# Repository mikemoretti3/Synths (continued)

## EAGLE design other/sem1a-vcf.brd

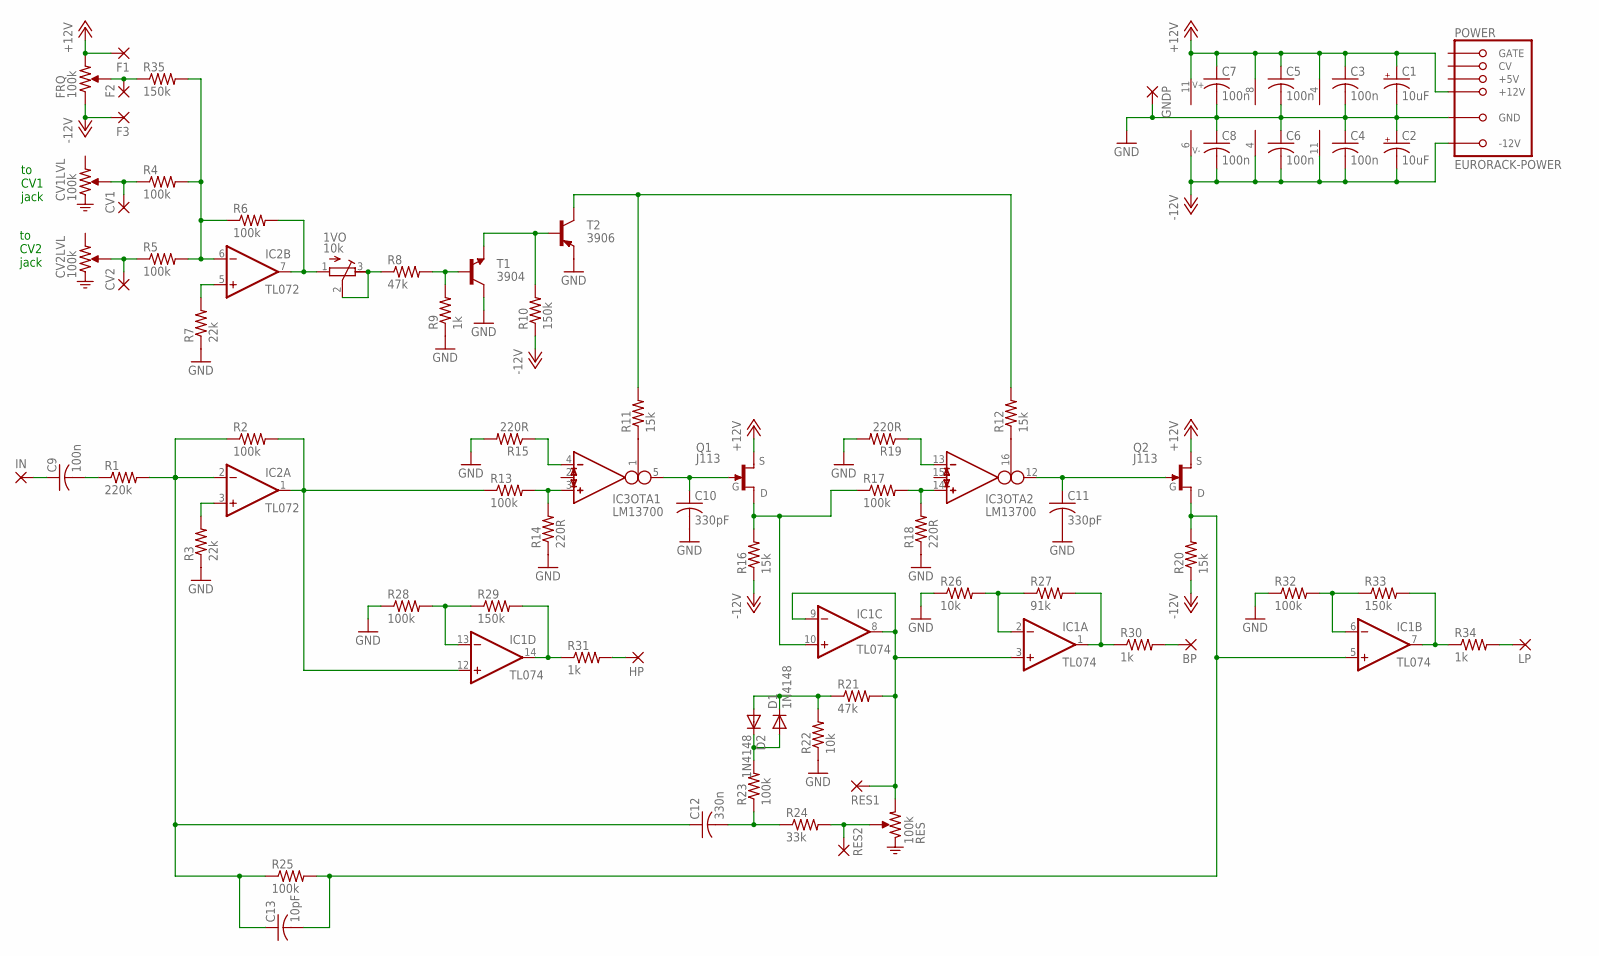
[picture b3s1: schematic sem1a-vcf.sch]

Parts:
1VO: 10k; RTRIM64W
BP: 2,54/1,0
C1, C2: 10uF; E2,5-5
C3, C4, C5, C6, C7, C8: 100n; C025-025X050
C9: 100n; C050-025X075
C10, C11: 330pF; C050-025X075
C12: 330n; C050-025X075
C13: 10pF; C050-025X075
CV1, CV2: 2,54/1,0
D1, D2: 1N4148; DO35-7
F1, F2, F3: 2,54/1,0
GNDP: 2,54/1,0
HP: 2,54/1,0
IC1: TL074; DIL14
IC2: TL072; DIL08
IC3: LM13700; DIL16
IN: 2,54/1,0
LP: 2,54/1,0
POWER: EURORACK-POWER; PINSHRD_PTH_2X8
Q1, Q2: J113; TO92-EBC
R1: 220k; 0207/10
R2, R6: 100k; 0207/2V
R3, R7: 22k; 0207/10
R4, R5, R13, R17, R23, R25, R28, R32: 100k; 0207/10
R8, R21: 47k; 0207/10
R9, R30, R31, R34: 1k; 0207/10
R10, R35: 150k; 0207/10
R11, R12, R16, R20: 15k; 0207/10
R14, R15, R18, R19: 220R; 0207/10
R22, R26: 10k; 0207/10
R24: 33k; 0207/10
R27: 91k; 0207/2V
R29, R33: 150k; 0207/2V
RES1, RES2: 2,54/1,0
T1: 3904; TO92-EBC
T2: 3906; TO92-EBC

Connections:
+12V: C1.+, C3.1, C5.1, C7.1, F1.1, IC1.4 (V+), IC2.8 (V+), IC3.11 (7), POWER.+12V@1 (+12V), POWER.+12V@2 (+12V), Q1.E (S), Q2.E (S)
-12V: C2.-, C4.2, C6.2, C8.2, F3.1, IC1.11 (V-), IC2.4 (V-), IC3.6 (4), POWER.-12V@1 (-12V), POWER.-12V@2 (-12V), R10.1, R16.1, R20.1
GND: C1.-, C2.+, C3.2, C4.1, C5.2, C6.1, C7.2, C8.1, C10.2, C11.2, GNDP.1, POWER.GND@1 (GND), POWER.GND@2 (GND), POWER.GND@3 (GND), POWER.GND@4 (GND), POWER.GND@5 (GND), POWER.GND@6 (GND), R3.1, R7.1, R9.1, R14.1, R15.2, R18.1, R19.2, R22.1, R26.1, R28.1, R32.1, T1.C, T2.E
unnamed: CV1.1, R4.1
unnamed: CV2.1, R5.1
unnamed: IC2.6 (-IN), R4.2, R5.2, R6.1, R35.2
unnamed: 1VO.2 (S), 1VO.3 (E), R8.1
unnamed: R10.2, T1.E, T2.B
unnamed: IC1.3 (+IN), IC1.8 (OUT), IC1.9 (-IN), R21.2, RES1.1
unnamed: R24.2, RES2.1
unnamed: R8.2, R9.2, T1.B
unnamed: IC3.1 (I_BIAS), R11.1
unnamed: C9.1, IN.1
unnamed: C9.2, R1.1
unnamed: C12.1, C13.1, IC2.2 (-IN), R1.2, R2.1, R25.1
unnamed: IC1.12 (+IN), IC2.1 (OUT), R2.2, R13.1
unnamed: IC2.3 (+IN), R3.2
unnamed: IC3.16 (I_BIAS), R12.1
unnamed: 1VO.1 (A), IC2.7 (OUT), R6.2
unnamed: IC2.5 (+IN), R7.2
unnamed: IC3.3 (IN_P), R13.2, R14.2
unnamed: IC3.4 (IN_N), R15.1
unnamed: C10.1, IC3.5 (OUT), Q1.C (G)
unnamed: IC1.10 (+IN), Q1.B (D), R16.2, R17.1
unnamed: IC3.13 (IN_N), R19.1
unnamed: IC3.14 (IN_P), R17.2, R18.2
unnamed: C11.1, IC3.12 (OUT), Q2.C (G)
unnamed: IC1.2 (-IN), R26.2, R27.1
unnamed: D1.C, D2.A, R21.1, R22.2
unnamed: D1.A, D2.C, R23.2
unnamed: R11.2, R12.2, T2.C
unnamed: C12.2, R23.1, R24.1
unnamed: C13.2, IC1.5 (+IN), Q2.B (D), R20.2, R25.2
unnamed: IC1.1 (OUT), R27.2, R30.1
unnamed: IC1.13 (-IN), R28.2, R29.1
unnamed: IC1.14 (OUT), R29.2, R31.1
unnamed: BP.1, R30.2
unnamed: HP.1, R31.2
unnamed: IC1.6 (-IN), R32.2, R33.1
unnamed: IC1.7 (OUT), R33.2, R34.1
unnamed: LP.1, R34.2
unnamed: F2.1, R35.1

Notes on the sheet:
to CV1 jack
to CV2 jack

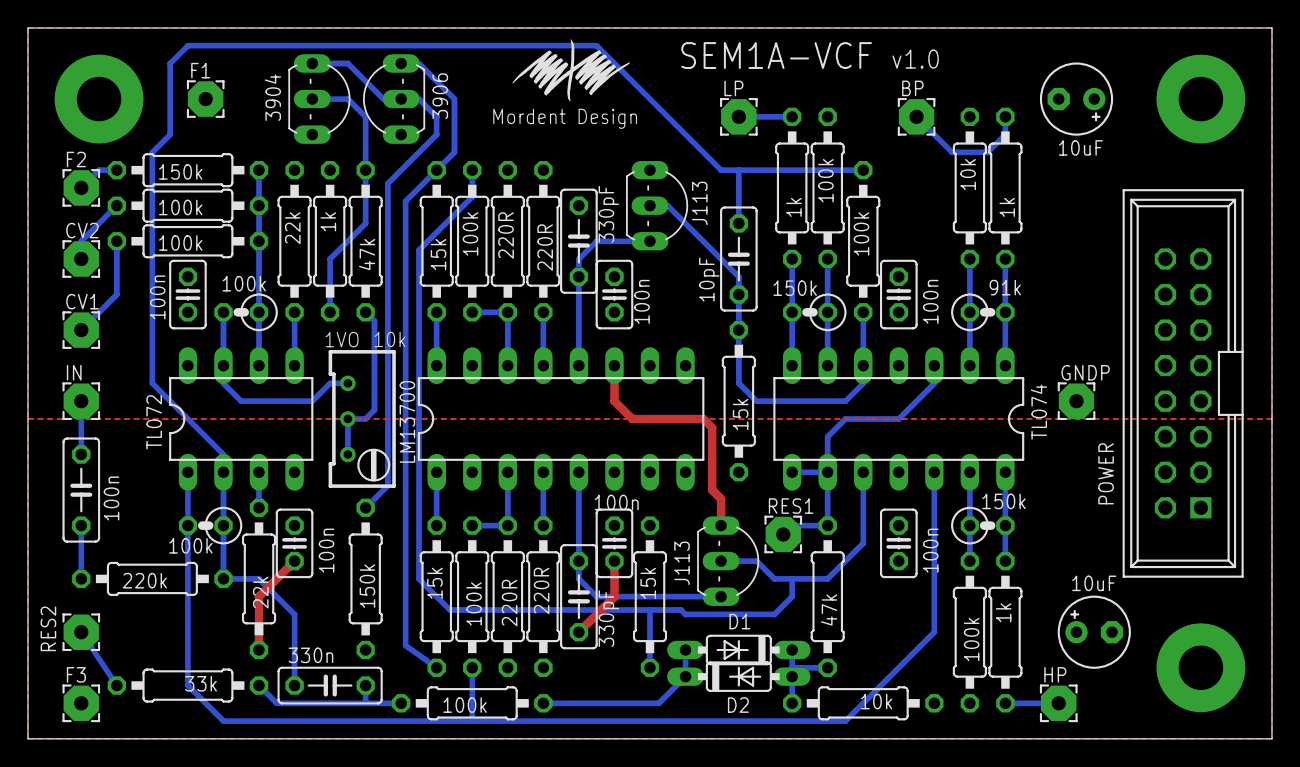
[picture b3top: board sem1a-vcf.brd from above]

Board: 2 copper layers, 88.9 x 50.8 mm, 71 parts (0 on the bottom side), 42 nets.

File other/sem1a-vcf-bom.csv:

Qty,Value,Device,Package,Parts,Description
10,100k,R-US_0207/10,0207/10,"R4, R5, R13, R17, R23, R25, R28, R32","RESISTOR, American symbol"
7,100n,C-US025-025X050,C025-025X050,"C3, C4, C5, C6, C7, C8","CAPACITOR, American symbol"
1,10k,R-TRIMM64W,RTRIM64W,1VO,Trimm resistor
2,10k,R-US_0207/10,0207/10,"R22, R26","RESISTOR, American symbol"
1,10pF,C-US050-025X075,C050-025X075,C13,"CAPACITOR, American symbol"
2,10uF,CPOL-USE2.5-5,"E2,5-5","C1, C2","POLARIZED CAPACITOR, American symbol"
4,150k,R-US_0207/10,0207/10,"R10, R35","RESISTOR, American symbol"
4,15k,R-US_0207/10,0207/10,"R11, R12, R16, R20","RESISTOR, American symbol"
2,1N4148,1N4148DO35-7,DO35-7,"D1, D2",DIODE
4,1k,R-US_0207/10,0207/10,"R9, R30, R31, R34","RESISTOR, American symbol"
4,220R,R-US_0207/10,0207/10,"R14, R15, R18, R19","RESISTOR, American symbol"
1,220k,R-US_0207/10,0207/10,R1,"RESISTOR, American symbol"
2,22k,R-US_0207/10,0207/10,"R3, R7","RESISTOR, American symbol"
1,330n,C-US050-025X075,C050-025X075,C12,"CAPACITOR, American symbol"
2,330pF,C-US050-025X075,C050-025X075,"C10, C11","CAPACITOR, American symbol"
1,33k,R-US_0207/10,0207/10,R24,"RESISTOR, American symbol"
1,3904,,TO92-EBC,T1,NPN Transistror
1,3906,,TO92-EBC,T2,PNP Transistror
2,47k,R-US_0207/10,0207/10,"R8, R21","RESISTOR, American symbol"
1,91k,R-US_0207/2V,0207/2V,R27,"RESISTOR, American symbol"
1,EURORACK-POWER,EURORACK-POWER,PINSHRD_PTH_2X8,POWER,
2,J113,J113/2N5457,TO92-EBC,"Q1, Q2",
1,LM13700,LM13700,DIL16,IC3,
1,TL072,TL072,DIL08,IC2,OP AMP
1,TL074,TL074,DIL14,IC1,OP AMP
